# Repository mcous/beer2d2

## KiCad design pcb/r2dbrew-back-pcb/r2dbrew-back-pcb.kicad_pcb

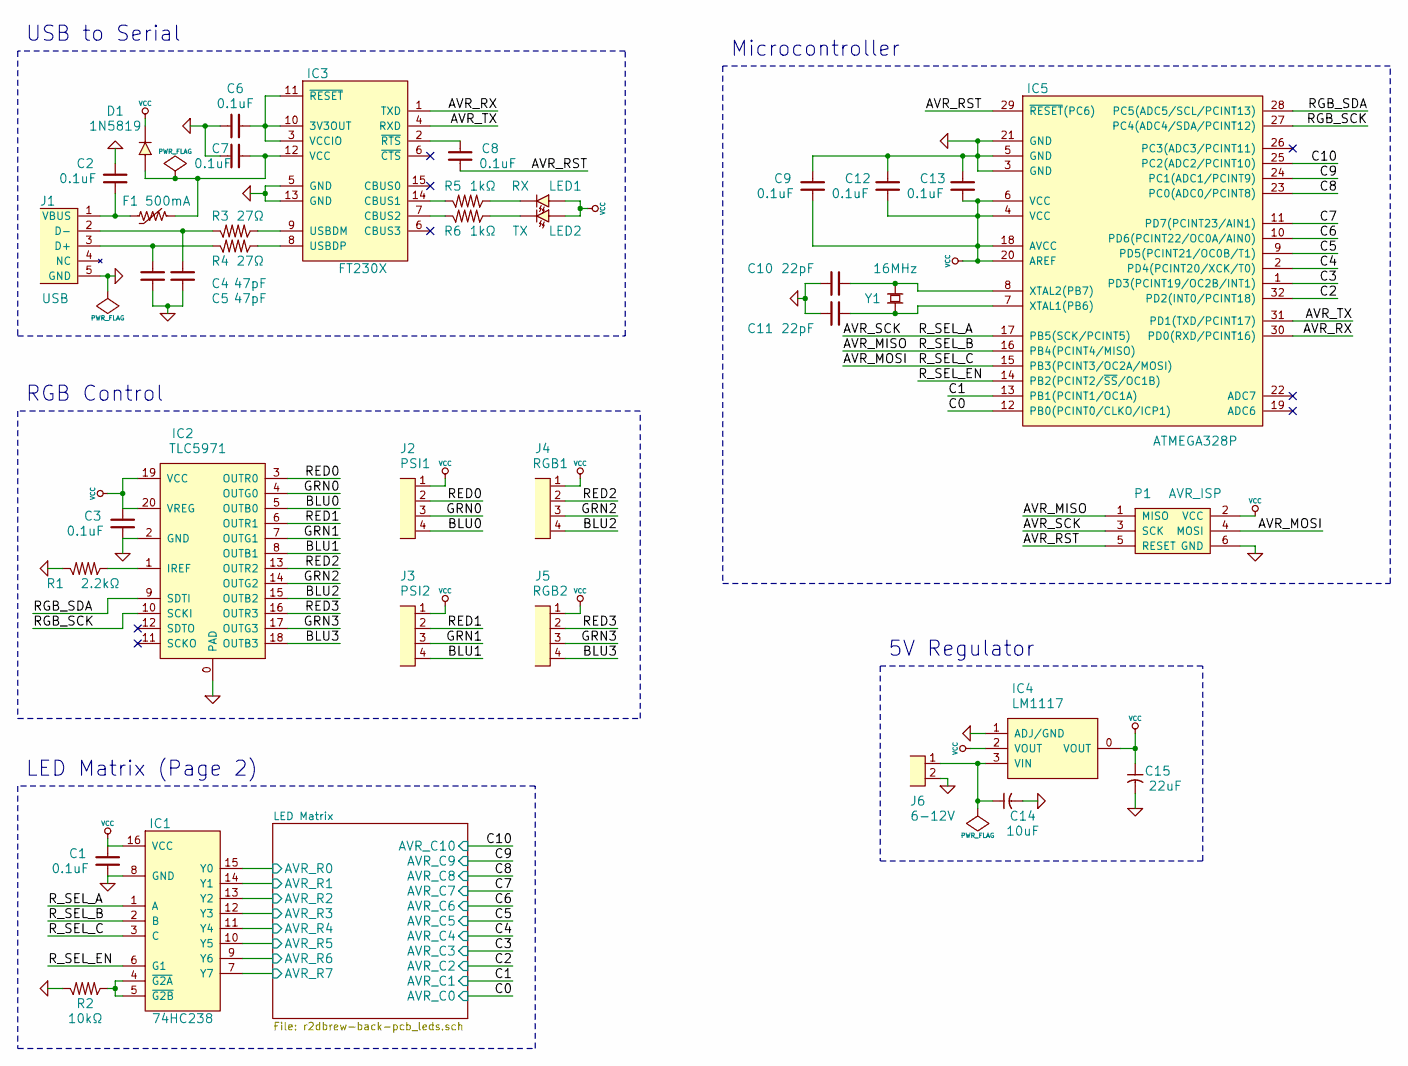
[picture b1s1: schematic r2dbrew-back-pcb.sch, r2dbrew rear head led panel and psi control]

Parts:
C1, C2, C3, C6, C7, C8, C9, C12, C13: 0.1uF
C4, C5: 47pF
C10, C11: 22pF
C14: 10uF
C15: 22uF
D1: 1N5819
F1: 500mA
IC1: 74HC238
IC2: TLC5971; Part TLC5971PWP
IC3: FT230X
IC4: LM1117
IC5: ATMEGA328P
J1: USB
J2: PSI1
J3: PSI2
J4: RGB1
J5: RGB2
J6: 6-12V
LED1: RX
LED2: TX
P1: AVR_ISP
R1: 2.2kΩ
R2: 10kΩ
R3, R4: 27Ω
R5, R6: 1kΩ
Y1: 16MHz

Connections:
/AVR_MISO: IC1.2 (B), IC5.16 (PB4(PCINT4/MISO)), P1.1 (MISO)
/AVR_MOSI: IC1.3 (C), IC5.15 (PB3(PCINT3/OC2A/MOSI)), P1.4 (MOSI)
/AVR_RST: C8.1, IC5.29 (~RESET~(PC6)), P1.5 (RESET)
/AVR_RX: IC3.1 (TXD), IC5.30 (PD0(RXD/PCINT16))
/AVR_SCK: IC1.1 (A), IC5.17 (PB5(SCK/PCINT5)), P1.3 (SCK)
/AVR_TX: IC3.4 (RXD), IC5.31 (PD1(TXD/PCINT17))
/BLU0: IC2.5 (OUTB0), J2.4
/BLU1: IC2.8 (OUTB1), J3.4
/BLU2: IC2.15 (OUTB2), J4.4
/BLU3: IC2.18 (OUTB3), J5.4
/GRN0: IC2.4 (OUTG0), J2.3
/GRN1: IC2.7 (OUTG1), J3.3
/GRN2: IC2.14 (OUTG2), J4.3
/GRN3: IC2.17 (OUTG3), J5.3
/LED Matrix/AVR_C0: IC5.12 (PB0(PCINT0/CLKO/ICP1)); also elsewhere on the board
/LED Matrix/AVR_C1: IC5.13 (PB1(PCINT1/OC1A)); also elsewhere on the board
/LED Matrix/AVR_C2: IC5.32 (PD2(INT0/PCINT18)); also elsewhere on the board
/LED Matrix/AVR_C3: IC5.1 (PD3(PCINT19/OC2B/INT1)); also elsewhere on the board
/LED Matrix/AVR_C4: IC5.2 (PD4(PCINT20/XCK/T0)); also elsewhere on the board
/LED Matrix/AVR_C5: IC5.9 (PD5(PCINT21/OC0B/T1)); also elsewhere on the board
/LED Matrix/AVR_C6: IC5.10 (PD6(PCINT22/OC0A/AIN0)); also elsewhere on the board
/LED Matrix/AVR_C7: IC5.11 (PD7(PCINT23/AIN1)); also elsewhere on the board
/LED Matrix/AVR_C8: IC5.23 (PC0(ADC0/PCINT8)); also elsewhere on the board
/LED Matrix/AVR_C9: IC5.24 (PC1(ADC1/PCINT9)); also elsewhere on the board
/LED Matrix/AVR_C10: IC5.25 (PC2(ADC2/PCINT10)); also elsewhere on the board
/LED Matrix/AVR_R0: IC1.15 (Y0); also elsewhere on the board
/LED Matrix/AVR_R1: IC1.14 (Y1); also elsewhere on the board
/LED Matrix/AVR_R2: IC1.13 (Y2); also elsewhere on the board
/LED Matrix/AVR_R3: IC1.12 (Y3); also elsewhere on the board
/LED Matrix/AVR_R4: IC1.11 (Y4); also elsewhere on the board
/LED Matrix/AVR_R5: IC1.10 (Y5); also elsewhere on the board
/LED Matrix/AVR_R6: IC1.9 (Y6); also elsewhere on the board
/LED Matrix/AVR_R7: IC1.7 (Y7); also elsewhere on the board
/RED0: IC2.3 (OUTR0), J2.2
/RED1: IC2.6 (OUTR1), J3.2
/RED2: IC2.13 (OUTR2), J4.2
/RED3: IC2.16 (OUTR3), J5.2
/RGB_SCK: IC2.10 (SCKI), IC5.27 (PC4(ADC4/SDA/PCINT12))
/RGB_SDA: IC2.9 (SDTI), IC5.28 (PC5(ADC5/SCL/PCINT13))
/R_SEL_EN: IC1.6 (G1), IC5.14 (PB2(PCINT2/~SS~/OC1B))
GND: C1.1, C2.2, C3.1, C4.1, C5.1, C6.1, C7.1, C9.1, C10.1, C11.1, C12.1, C13.1, C14.2, C15.2, IC1.8 (GND), IC2.0 (PAD), IC2.2 (GND), IC3.5 (GND), IC3.13 (GND), IC4.1 (ADJ/GND), IC5.3 (GND), IC5.5 (GND), IC5.21 (GND), J1.5 (GND), J6.2, P1.6 (GND), R1.1, R2.1; also elsewhere on the board
unnamed: C2.1, F1.1, J1.1 (VBUS)
unnamed: C4.2, J1.3 (D+), R4.1
unnamed: C5.2, J1.2 (D-), R3.1
unnamed: C6.2, IC3.3 (VCCIO), IC3.10 (3V3OUT), IC3.11 (~RESET~)
unnamed: C7.2, D1.2 (A), F1.2, IC3.12 (VCC)
unnamed: C8.2, IC3.2 (~RTS~)
unnamed: C10.2, IC5.8 (XTAL2(PB7)), Y1.2
unnamed: C11.2, IC5.7 (XTAL1(PB6)), Y1.1
unnamed: C14.1, IC4.3 (VIN), J6.1
unnamed: IC1.4 (~G2A~), IC1.5 (~G2B~), R2.2
unnamed: IC2.1 (IREF), R1.2
unnamed: IC3.7 (CBUS2), R6.1
unnamed: IC3.8 (USBDP), R4.2
unnamed: IC3.9 (USBDM), R3.2
unnamed: IC3.14 (CBUS1), R5.1
unnamed: LED1.1 (C), R5.2
unnamed: LED2.1 (C), R6.2
VCC: C1.2, C3.2, C9.2, C12.2, C13.2, C15.1, D1.1 (C), IC1.16 (VCC), IC2.19 (VCC), IC2.20 (VREG), IC4.0 (VOUT), IC4.2 (VOUT), IC5.4 (VCC), IC5.6 (VCC), IC5.18 (AVCC), IC5.20 (AREF), J2.1, J3.1, J4.1, J5.1, LED1.2 (A), LED2.2 (A), P1.2 (VCC); also elsewhere on the board

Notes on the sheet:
LED Matrix (Page 2)
RGB Control
USB to Serial
Microcontroller
5V Regulator

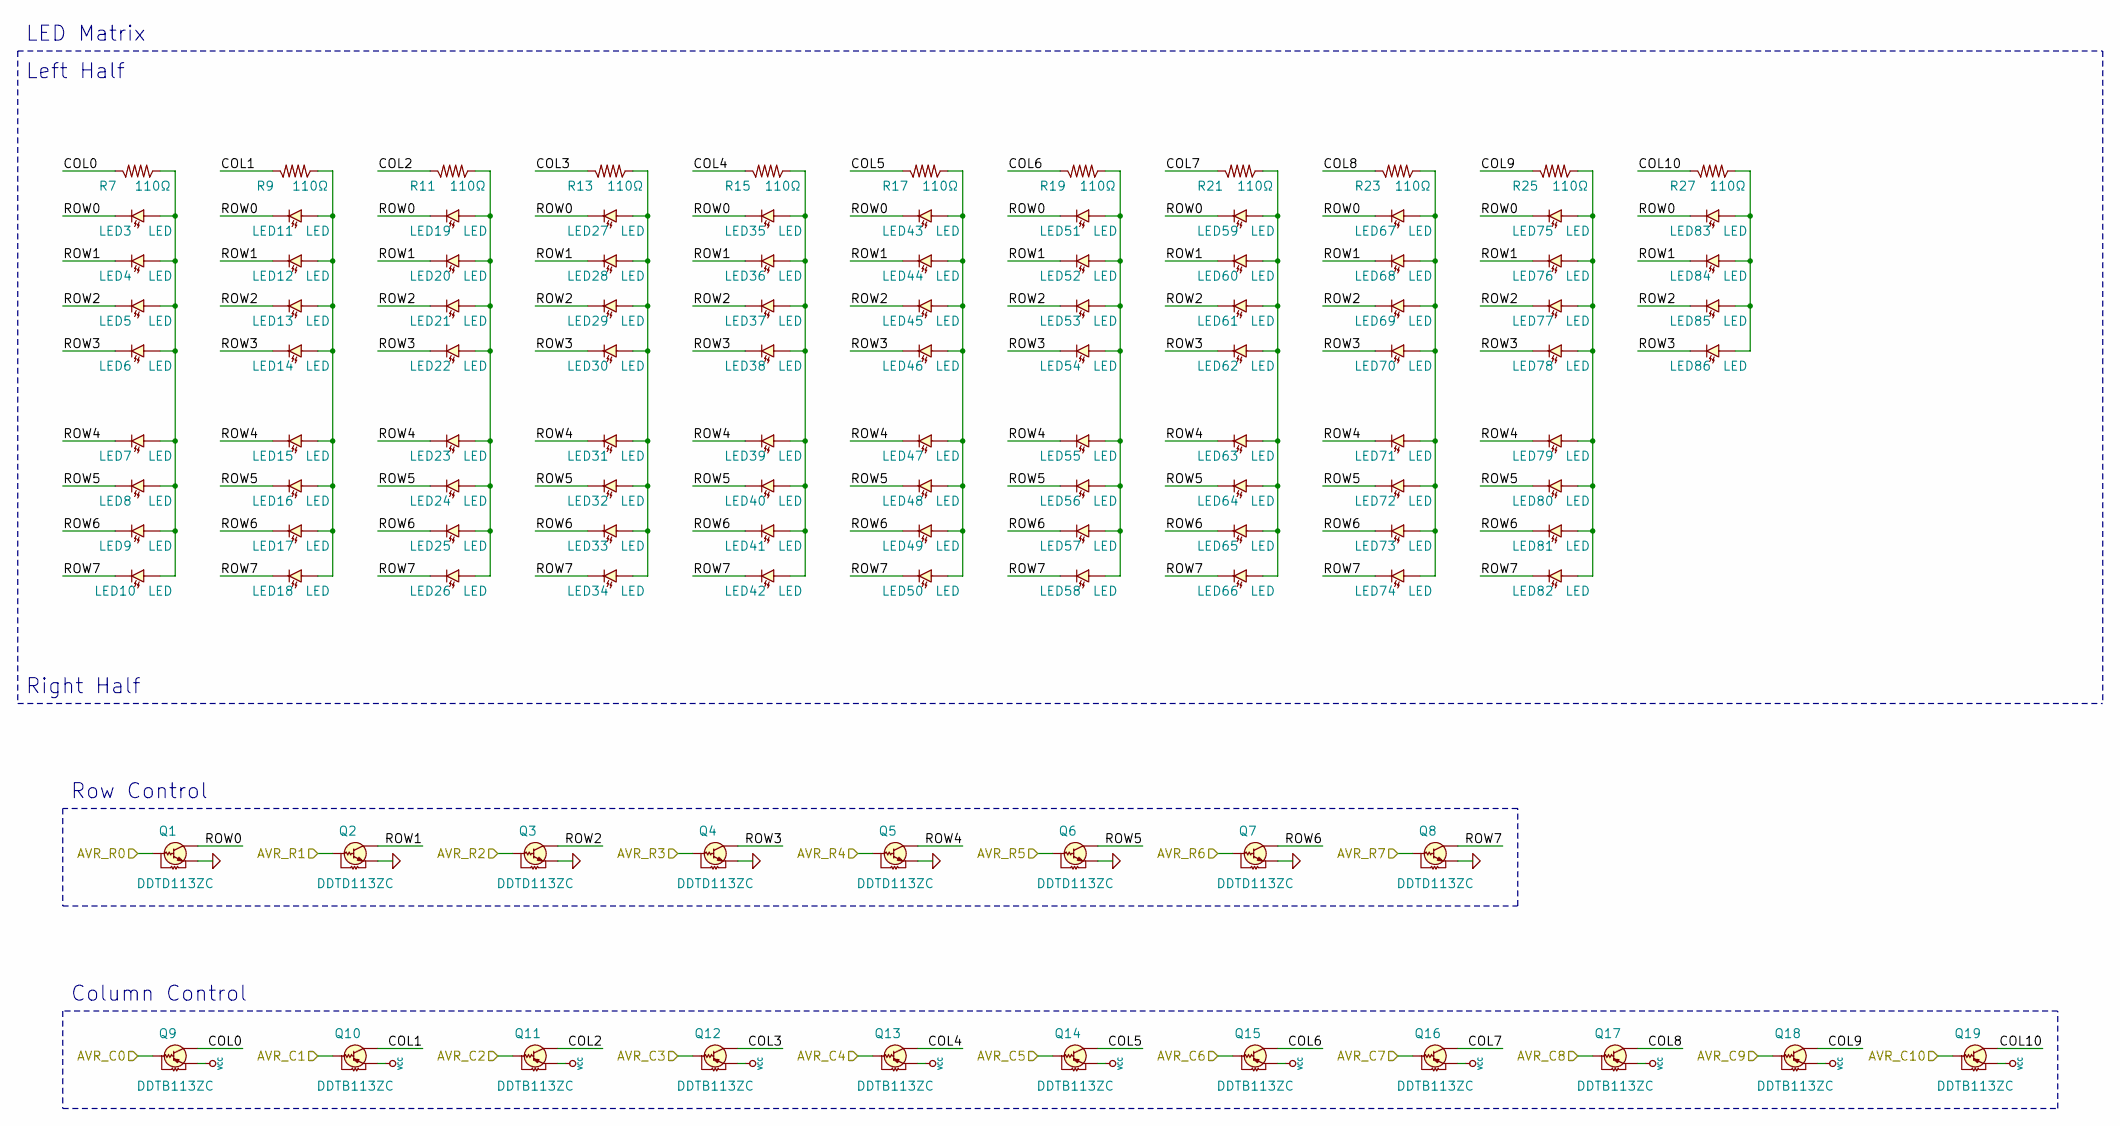
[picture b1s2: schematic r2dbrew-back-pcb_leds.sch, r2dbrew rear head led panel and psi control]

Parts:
LED3, LED4, LED5, LED6, LED7, LED8, LED9, LED10, LED11, LED12, LED13, LED14, LED15, LED16, LED17, LED18, LED19, LED20, LED21, LED22, LED23, LED24, LED25, LED26, LED27, LED28, LED29, LED30, LED31, LED32, LED33, LED34, LED35, LED36, LED37, LED38, LED39, LED40, LED41, LED42, LED43, LED44, LED45, LED46, LED47, LED48, LED49, LED50, LED51, LED52, LED53, LED54, LED55, LED56, LED57, LED58, LED59, LED60, LED61, LED62, LED63, LED64, LED65, LED66, LED67, LED68, LED69, LED70, LED71, LED72, LED73, LED74, LED75, LED76, LED77, LED78, LED79, LED80, LED81, LED82, LED83, LED84, LED85, LED86: LED
Q1, Q2, Q3, Q4, Q5, Q6, Q7, Q8: DDTD113ZC
Q9, Q10, Q11, Q12, Q13, Q14, Q15, Q16, Q17, Q18, Q19: DDTB113ZC
R7, R9, R11, R13, R15, R17, R19, R21, R23, R25, R27: 110Ω

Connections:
/LED Matrix/AVR_C0: Q9.1 (B); also elsewhere on the board
/LED Matrix/AVR_C1: Q10.1 (B); also elsewhere on the board
/LED Matrix/AVR_C2: Q11.1 (B); also elsewhere on the board
/LED Matrix/AVR_C3: Q12.1 (B); also elsewhere on the board
/LED Matrix/AVR_C4: Q13.1 (B); also elsewhere on the board
/LED Matrix/AVR_C5: Q14.1 (B); also elsewhere on the board
/LED Matrix/AVR_C6: Q15.1 (B); also elsewhere on the board
/LED Matrix/AVR_C7: Q16.1 (B); also elsewhere on the board
/LED Matrix/AVR_C8: Q17.1 (B); also elsewhere on the board
/LED Matrix/AVR_C9: Q18.1 (B); also elsewhere on the board
/LED Matrix/AVR_C10: Q19.1 (B); also elsewhere on the board
/LED Matrix/AVR_R0: Q1.1 (B); also elsewhere on the board
/LED Matrix/AVR_R1: Q2.1 (B); also elsewhere on the board
/LED Matrix/AVR_R2: Q3.1 (B); also elsewhere on the board
/LED Matrix/AVR_R3: Q4.1 (B); also elsewhere on the board
/LED Matrix/AVR_R4: Q5.1 (B); also elsewhere on the board
/LED Matrix/AVR_R5: Q6.1 (B); also elsewhere on the board
/LED Matrix/AVR_R6: Q7.1 (B); also elsewhere on the board
/LED Matrix/AVR_R7: Q8.1 (B); also elsewhere on the board
/LED Matrix/COL0: Q9.3 (C), R7.1
/LED Matrix/COL1: Q10.3 (C), R9.1
/LED Matrix/COL2: Q11.3 (C), R11.1
/LED Matrix/COL3: Q12.3 (C), R13.1
/LED Matrix/COL4: Q13.3 (C), R15.1
/LED Matrix/COL5: Q14.3 (C), R17.1
/LED Matrix/COL6: Q15.3 (C), R19.1
/LED Matrix/COL7: Q16.3 (C), R21.1
/LED Matrix/COL8: Q17.3 (C), R23.1
/LED Matrix/COL9: Q18.3 (C), R25.1
/LED Matrix/COL10: Q19.3 (C), R27.1
/LED Matrix/ROW0: LED3.1 (C), LED11.1 (C), LED19.1 (C), LED27.1 (C), LED35.1 (C), LED43.1 (C), LED51.1 (C), LED59.1 (C), LED67.1 (C), LED75.1 (C), LED83.1 (C), Q1.3 (C)
/LED Matrix/ROW1: LED4.1 (C), LED12.1 (C), LED20.1 (C), LED28.1 (C), LED36.1 (C), LED44.1 (C), LED52.1 (C), LED60.1 (C), LED68.1 (C), LED76.1 (C), LED84.1 (C), Q2.3 (C)
/LED Matrix/ROW2: LED5.1 (C), LED13.1 (C), LED21.1 (C), LED29.1 (C), LED37.1 (C), LED45.1 (C), LED53.1 (C), LED61.1 (C), LED69.1 (C), LED77.1 (C), LED85.1 (C), Q3.3 (C)
/LED Matrix/ROW3: LED6.1 (C), LED14.1 (C), LED22.1 (C), LED30.1 (C), LED38.1 (C), LED46.1 (C), LED54.1 (C), LED62.1 (C), LED70.1 (C), LED78.1 (C), LED86.1 (C), Q4.3 (C)
/LED Matrix/ROW4: LED7.1 (C), LED15.1 (C), LED23.1 (C), LED31.1 (C), LED39.1 (C), LED47.1 (C), LED55.1 (C), LED63.1 (C), LED71.1 (C), LED79.1 (C), Q5.3 (C)
/LED Matrix/ROW5: LED8.1 (C), LED16.1 (C), LED24.1 (C), LED32.1 (C), LED40.1 (C), LED48.1 (C), LED56.1 (C), LED64.1 (C), LED72.1 (C), LED80.1 (C), Q6.3 (C)
/LED Matrix/ROW6: LED9.1 (C), LED17.1 (C), LED25.1 (C), LED33.1 (C), LED41.1 (C), LED49.1 (C), LED57.1 (C), LED65.1 (C), LED73.1 (C), LED81.1 (C), Q7.3 (C)
/LED Matrix/ROW7: LED10.1 (C), LED18.1 (C), LED26.1 (C), LED34.1 (C), LED42.1 (C), LED50.1 (C), LED58.1 (C), LED66.1 (C), LED74.1 (C), LED82.1 (C), Q8.3 (C)
GND: Q1.2 (E), Q2.2 (E), Q3.2 (E), Q4.2 (E), Q5.2 (E), Q6.2 (E), Q7.2 (E), Q8.2 (E); also elsewhere on the board
unnamed: LED3.2 (A), LED4.2 (A), LED5.2 (A), LED6.2 (A), LED7.2 (A), LED8.2 (A), LED9.2 (A), LED10.2 (A), R7.2
unnamed: LED11.2 (A), LED12.2 (A), LED13.2 (A), LED14.2 (A), LED15.2 (A), LED16.2 (A), LED17.2 (A), LED18.2 (A), R9.2
unnamed: LED19.2 (A), LED20.2 (A), LED21.2 (A), LED22.2 (A), LED23.2 (A), LED24.2 (A), LED25.2 (A), LED26.2 (A), R11.2
unnamed: LED27.2 (A), LED28.2 (A), LED29.2 (A), LED30.2 (A), LED31.2 (A), LED32.2 (A), LED33.2 (A), LED34.2 (A), R13.2
unnamed: LED35.2 (A), LED36.2 (A), LED37.2 (A), LED38.2 (A), LED39.2 (A), LED40.2 (A), LED41.2 (A), LED42.2 (A), R15.2
unnamed: LED43.2 (A), LED44.2 (A), LED45.2 (A), LED46.2 (A), LED47.2 (A), LED48.2 (A), LED49.2 (A), LED50.2 (A), R17.2
unnamed: LED51.2 (A), LED52.2 (A), LED53.2 (A), LED54.2 (A), LED55.2 (A), LED56.2 (A), LED57.2 (A), LED58.2 (A), R19.2
unnamed: LED59.2 (A), LED60.2 (A), LED61.2 (A), LED62.2 (A), LED63.2 (A), LED64.2 (A), LED65.2 (A), LED66.2 (A), R21.2
unnamed: LED67.2 (A), LED68.2 (A), LED69.2 (A), LED70.2 (A), LED71.2 (A), LED72.2 (A), LED73.2 (A), LED74.2 (A), R23.2
unnamed: LED75.2 (A), LED76.2 (A), LED77.2 (A), LED78.2 (A), LED79.2 (A), LED80.2 (A), LED81.2 (A), LED82.2 (A), R25.2
unnamed: LED83.2 (A), LED84.2 (A), LED85.2 (A), LED86.2 (A), R27.2
VCC: Q9.2 (E), Q10.2 (E), Q11.2 (E), Q12.2 (E), Q13.2 (E), Q14.2 (E), Q15.2 (E), Q16.2 (E), Q17.2 (E), Q18.2 (E), Q19.2 (E); also elsewhere on the board

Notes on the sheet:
LED Matrix
Right Half
Row Control
Column Control
Left Half

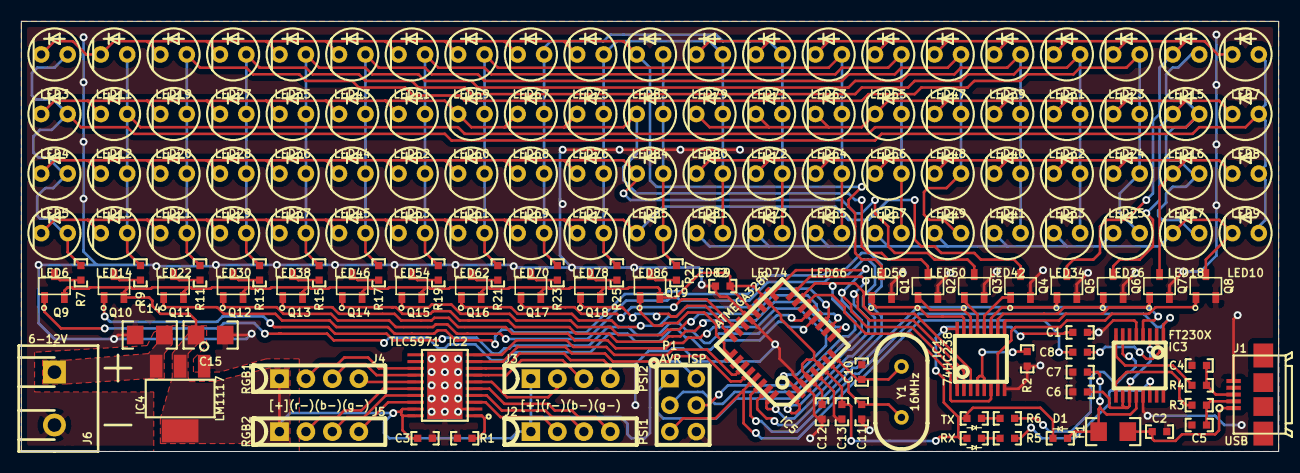
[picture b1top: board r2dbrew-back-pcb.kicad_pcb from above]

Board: 2 copper layers, 120.6 x 41.3 mm, 152 parts (0 on the bottom side), 89 nets.

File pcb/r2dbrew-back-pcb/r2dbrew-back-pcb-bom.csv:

Reference, Value, Footprint, Datasheet, Manufacturer, Part
J6,6-12V,,
IC4,LM1117,,
C14,10uF,,
C15,22uF,,
IC5,ATMEGA328P,,
IC1,74HC238,,
C1,0.1uF,,
R2,10kΩ,,
Y1,16MHz,,
C11,22pF,,
C10,22pF,,
C13,0.1uF,,
C12,0.1uF,,
C9,0.1uF,,
P1,AVR_ISP,,
J1,USB,,
R3,27Ω,,
R4,27Ω,,
C4,47pF,,
C5,47pF,,
IC3,FT230X,,
C6,0.1uF,,
C7,0.1uF,,
C2,0.1uF,,
F1,500mA,,
D1,1N5819,,
C8,0.1uF,,
R5,1kΩ,,
R6,1kΩ,,
LED1,RX,,
LED2,TX,,
IC2,TLC5971,,,TI,TLC5971PWP
C3,0.1uF,,
R1,2.2kΩ,,
J2,PSI1,,
J3,PSI2,,
J4,RGB1,,
J5,RGB2,,
LED4,LED,,
LED5,LED,,
LED6,LED,,
Q1,DDTD113ZC,,
Q2,DDTD113ZC,,
Q3,DDTD113ZC,,
Q4,DDTD113ZC,,
Q5,DDTD113ZC,,
Q6,DDTD113ZC,,
Q7,DDTD113ZC,,
Q8,DDTD113ZC,,
Q9,DDTB113ZC,,
Q10,DDTB113ZC,,
Q11,DDTB113ZC,,
Q12,DDTB113ZC,,
Q13,DDTB113ZC,,
Q14,DDTB113ZC,,
Q15,DDTB113ZC,,
Q16,DDTB113ZC,,
Q17,DDTB113ZC,,
Q18,DDTB113ZC,,
Q19,DDTB113ZC,,
R7,110Ω,,
LED3,LED,,
LED12,LED,,
LED13,LED,,
LED14,LED,,
R9,110Ω,,
LED11,LED,,
LED20,LED,,
LED21,LED,,
LED22,LED,,
R11,110Ω,,
LED19,LED,,
LED28,LED,,
LED29,LED,,
LED30,LED,,
R13,110Ω,,
LED27,LED,,
LED36,LED,,
LED37,LED,,
LED38,LED,,
R15,110Ω,,
LED35,LED,,
LED44,LED,,
LED45,LED,,
LED46,LED,,
R17,110Ω,,
LED43,LED,,
LED52,LED,,
LED53,LED,,
LED54,LED,,
R19,110Ω,,
LED51,LED,,
LED60,LED,,
LED61,LED,,
LED62,LED,,
R21,110Ω,,
LED59,LED,,
LED68,LED,,
LED69,LED,,
LED70,LED,,
R23,110Ω,,
LED67,LED,,
LED76,LED,,
LED77,LED,,
LED78,LED,,
R25,110Ω,,
LED75,LED,,
LED84,LED,,
LED85,LED,,
LED86,LED,,
R27,110Ω,,
LED83,LED,,
LED8,LED,,
LED9,LED,,
LED10,LED,,
LED7,LED,,
LED16,LED,,
LED17,LED,,
LED18,LED,,
LED15,LED,,
LED24,LED,,
LED25,LED,,
LED26,LED,,
LED23,LED,,
LED32,LED,,
LED33,LED,,
LED34,LED,,
LED31,LED,,
LED40,LED,,
LED41,LED,,
LED42,LED,,
LED39,LED,,
LED48,LED,,
LED49,LED,,
LED50,LED,,
LED47,LED,,
LED56,LED,,
LED57,LED,,
LED58,LED,,
LED55,LED,,
LED64,LED,,
LED65,LED,,
LED66,LED,,
LED63,LED,,
LED72,LED,,
LED73,LED,,
LED74,LED,,
LED71,LED,,
LED80,LED,,
LED81,LED,,
LED82,LED,,
LED79,LED,,

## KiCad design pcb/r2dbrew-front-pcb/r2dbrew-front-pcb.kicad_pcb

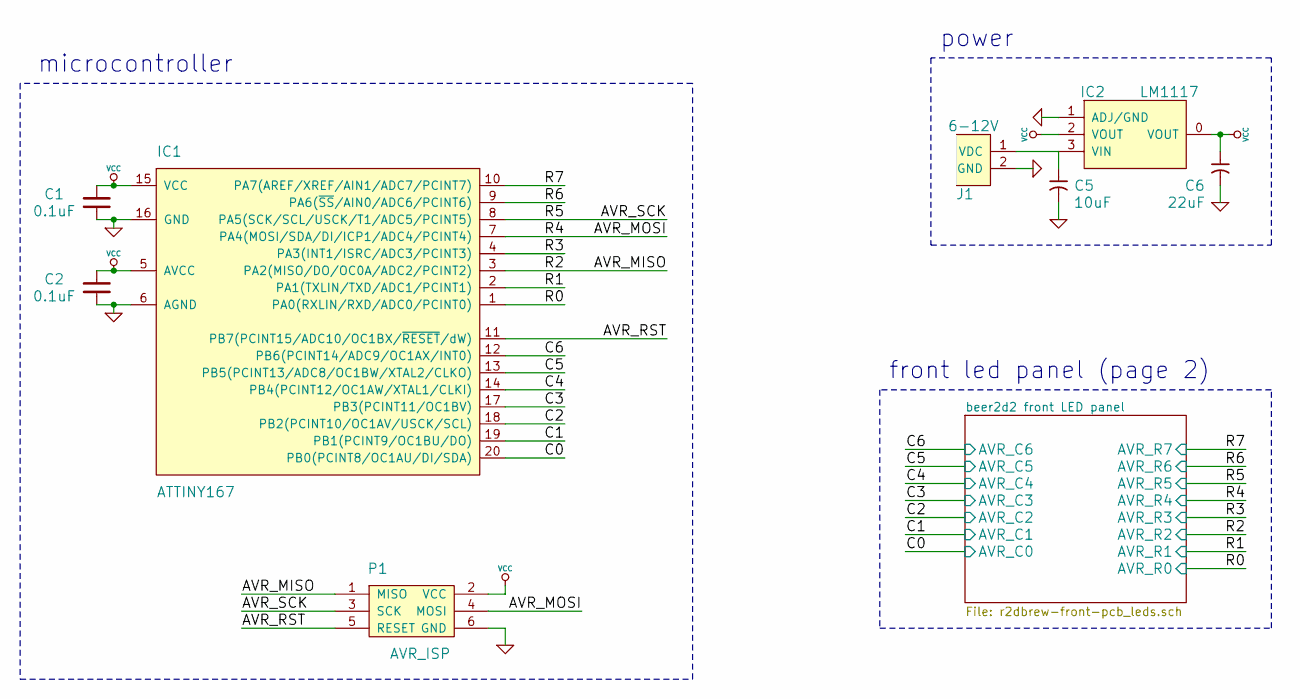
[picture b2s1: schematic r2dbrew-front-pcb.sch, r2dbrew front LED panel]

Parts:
C1, C2: 0.1uF
C5: 10uF
C6: 22uF
IC1: ATTINY167
IC2: LM1117
J1: 6-12V
P1: AVR_ISP

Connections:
/AVR_RST: IC1.11 (PB7(PCINT15/ADC10/OC1BX/~RESET~/dW)), P1.5 (RESET)
/beer2d2 front LED panel/AVR_C0: IC1.20 (PB0(PCINT8/OC1AU/DI/SDA)); also elsewhere on the board
/beer2d2 front LED panel/AVR_C1: IC1.19 (PB1(PCINT9/OC1BU/DO)); also elsewhere on the board
/beer2d2 front LED panel/AVR_C2: IC1.18 (PB2(PCINT10/OC1AV/USCK/SCL)); also elsewhere on the board
/beer2d2 front LED panel/AVR_C3: IC1.17 (PB3(PCINT11/OC1BV)); also elsewhere on the board
/beer2d2 front LED panel/AVR_C4: IC1.14 (PB4(PCINT12/OC1AW/XTAL1/CLKI)); also elsewhere on the board
/beer2d2 front LED panel/AVR_C5: IC1.13 (PB5(PCINT13/ADC8/OC1BW/XTAL2/CLKO)); also elsewhere on the board
/beer2d2 front LED panel/AVR_C6: IC1.12 (PB6(PCINT14/ADC9/OC1AX/INT0)); also elsewhere on the board
/beer2d2 front LED panel/AVR_R0: IC1.1 (PA0(RXLIN/RXD/ADC0/PCINT0)); also elsewhere on the board
/beer2d2 front LED panel/AVR_R1: IC1.2 (PA1(TXLIN/TXD/ADC1/PCINT1)); also elsewhere on the board
/beer2d2 front LED panel/AVR_R2: IC1.3 (PA2(MISO/DO/OC0A/ADC2/PCINT2)), P1.1 (MISO); also elsewhere on the board
/beer2d2 front LED panel/AVR_R3: IC1.4 (PA3(INT1/ISRC/ADC3/PCINT3)); also elsewhere on the board
/beer2d2 front LED panel/AVR_R4: IC1.7 (PA4(MOSI/SDA/DI/ICP1/ADC4/PCINT4)), P1.4 (MOSI); also elsewhere on the board
/beer2d2 front LED panel/AVR_R5: IC1.8 (PA5(SCK/SCL/USCK/T1/ADC5/PCINT5)), P1.3 (SCK); also elsewhere on the board
/beer2d2 front LED panel/AVR_R6: IC1.9 (PA6(~SS~/AIN0/ADC6/PCINT6)); also elsewhere on the board
/beer2d2 front LED panel/AVR_R7: IC1.10 (PA7(AREF/XREF/AIN1/ADC7/PCINT7)); also elsewhere on the board
GND: C1.1, C2.1, C5.2, C6.2, IC1.6 (AGND), IC1.16 (GND), IC2.1 (ADJ/GND), J1.2 (GND), P1.6 (GND); also elsewhere on the board
unnamed: C5.1, IC2.3 (VIN), J1.1 (VDC)
VCC: C1.2, C2.2, C6.1, IC1.5 (AVCC), IC1.15 (VCC), IC2.0 (VOUT), IC2.2 (VOUT), P1.2 (VCC); also elsewhere on the board

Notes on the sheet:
power
microcontroller
front led panel (page 2)

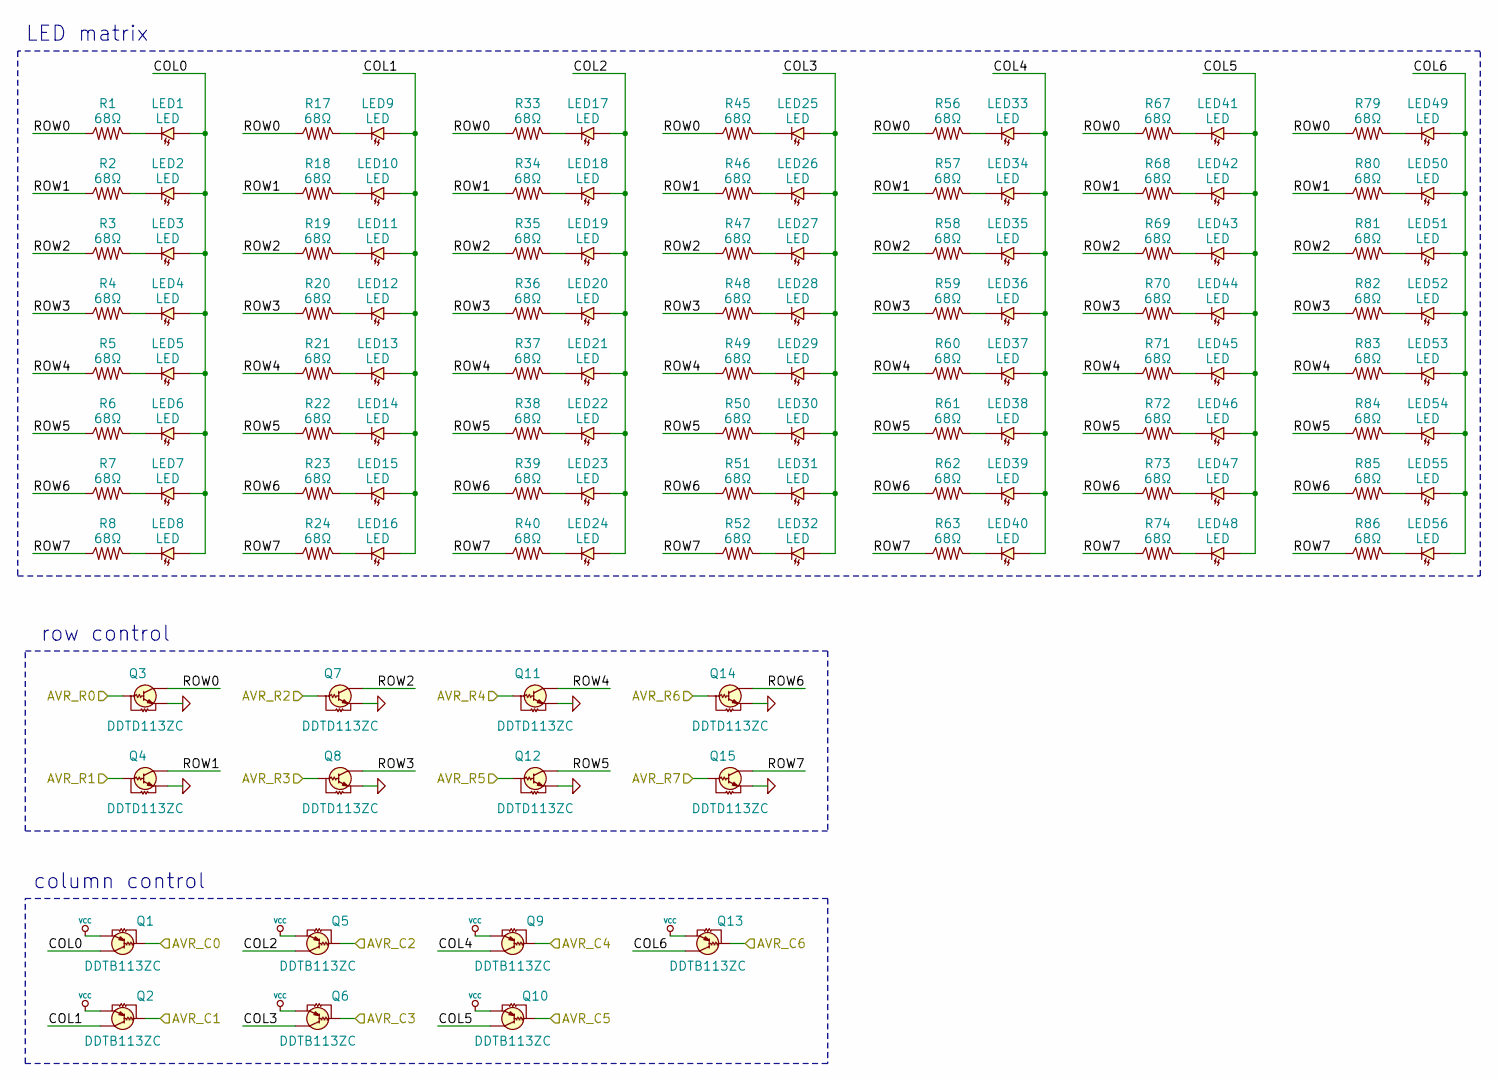
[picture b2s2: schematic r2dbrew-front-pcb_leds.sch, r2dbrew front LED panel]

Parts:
LED1, LED2, LED3, LED4, LED5, LED6, LED7, LED8, LED9, LED10, LED11, LED12, LED13, LED14, LED15, LED16, LED17, LED18, LED19, LED20, LED21, LED22, LED23, LED24, LED25, LED26, LED27, LED28, LED29, LED30, LED31, LED32, LED33, LED34, LED35, LED36, LED37, LED38, LED39, LED40, LED41, LED42, LED43, LED44, LED45, LED46, LED47, LED48, LED49, LED50, LED51, LED52, LED53, LED54, LED55, LED56: LED
Q1, Q2, Q5, Q6, Q9, Q10, Q13: DDTB113ZC; Part DDTB113ZC-7-F
Q3, Q4, Q7, Q8, Q11, Q12, Q14, Q15: DDTD113ZC; Part DDTD113ZC-7-F
R1, R2, R3, R4, R5, R6, R7, R8, R17, R18, R19, R20, R21, R22, R23, R24, R33, R34, R35, R36, R37, R38, R39, R40, R45, R46, R47, R48, R49, R50, R51, R52, R56, R57, R58, R59, R60, R61, R62, R63, R67, R68, R69, R70, R71, R72, R73, R74, R79, R80, R81, R82, R83, R84, R85, R86: 68Ω; Part RC1608J680CS

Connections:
/beer2d2 front LED panel/AVR_C0: Q1.1 (B); also elsewhere on the board
/beer2d2 front LED panel/AVR_C1: Q2.1 (B); also elsewhere on the board
/beer2d2 front LED panel/AVR_C2: Q5.1 (B); also elsewhere on the board
/beer2d2 front LED panel/AVR_C3: Q6.1 (B); also elsewhere on the board
/beer2d2 front LED panel/AVR_C4: Q9.1 (B); also elsewhere on the board
/beer2d2 front LED panel/AVR_C5: Q10.1 (B); also elsewhere on the board
/beer2d2 front LED panel/AVR_C6: Q13.1 (B); also elsewhere on the board
/beer2d2 front LED panel/AVR_R0: Q3.1 (B); also elsewhere on the board
/beer2d2 front LED panel/AVR_R1: Q4.1 (B); also elsewhere on the board
/beer2d2 front LED panel/AVR_R2: Q7.1 (B); also elsewhere on the board
/beer2d2 front LED panel/AVR_R3: Q8.1 (B); also elsewhere on the board
/beer2d2 front LED panel/AVR_R4: Q11.1 (B); also elsewhere on the board
/beer2d2 front LED panel/AVR_R5: Q12.1 (B); also elsewhere on the board
/beer2d2 front LED panel/AVR_R6: Q14.1 (B); also elsewhere on the board
/beer2d2 front LED panel/AVR_R7: Q15.1 (B); also elsewhere on the board
/beer2d2 front LED panel/COL0: LED1.2 (A), LED2.2 (A), LED3.2 (A), LED4.2 (A), LED5.2 (A), LED6.2 (A), LED7.2 (A), LED8.2 (A), Q1.3 (C)
/beer2d2 front LED panel/COL1: LED9.2 (A), LED10.2 (A), LED11.2 (A), LED12.2 (A), LED13.2 (A), LED14.2 (A), LED15.2 (A), LED16.2 (A), Q2.3 (C)
/beer2d2 front LED panel/COL2: LED17.2 (A), LED18.2 (A), LED19.2 (A), LED20.2 (A), LED21.2 (A), LED22.2 (A), LED23.2 (A), LED24.2 (A), Q5.3 (C)
/beer2d2 front LED panel/COL3: LED25.2 (A), LED26.2 (A), LED27.2 (A), LED28.2 (A), LED29.2 (A), LED30.2 (A), LED31.2 (A), LED32.2 (A), Q6.3 (C)
/beer2d2 front LED panel/COL4: LED33.2 (A), LED34.2 (A), LED35.2 (A), LED36.2 (A), LED37.2 (A), LED38.2 (A), LED39.2 (A), LED40.2 (A), Q9.3 (C)
/beer2d2 front LED panel/COL5: LED41.2 (A), LED42.2 (A), LED43.2 (A), LED44.2 (A), LED45.2 (A), LED46.2 (A), LED47.2 (A), LED48.2 (A), Q10.3 (C)
/beer2d2 front LED panel/COL6: LED49.2 (A), LED50.2 (A), LED51.2 (A), LED52.2 (A), LED53.2 (A), LED54.2 (A), LED55.2 (A), LED56.2 (A), Q13.3 (C)
/beer2d2 front LED panel/ROW0: Q3.3 (C), R1.2, R17.2, R33.2, R45.2, R56.2, R67.2, R79.2
/beer2d2 front LED panel/ROW1: Q4.3 (C), R2.2, R18.2, R34.2, R46.2, R57.2, R68.2, R80.2
/beer2d2 front LED panel/ROW2: Q7.3 (C), R3.2, R19.2, R35.2, R47.2, R58.2, R69.2, R81.2
/beer2d2 front LED panel/ROW3: Q8.3 (C), R4.2, R20.2, R36.2, R48.2, R59.2, R70.2, R82.2
/beer2d2 front LED panel/ROW4: Q11.3 (C), R5.2, R21.2, R37.2, R49.2, R60.2, R71.2, R83.2
/beer2d2 front LED panel/ROW5: Q12.3 (C), R6.2, R22.2, R38.2, R50.2, R61.2, R72.2, R84.2
/beer2d2 front LED panel/ROW6: Q14.3 (C), R7.2, R23.2, R39.2, R51.2, R62.2, R73.2, R85.2
/beer2d2 front LED panel/ROW7: Q15.3 (C), R8.2, R24.2, R40.2, R52.2, R63.2, R74.2, R86.2
GND: Q3.2 (E), Q4.2 (E), Q7.2 (E), Q8.2 (E), Q11.2 (E), Q12.2 (E), Q14.2 (E), Q15.2 (E); also elsewhere on the board
unnamed: LED1.1 (C), R1.1
unnamed: LED2.1 (C), R2.1
unnamed: LED3.1 (C), R3.1
unnamed: LED4.1 (C), R4.1
unnamed: LED5.1 (C), R5.1
unnamed: LED6.1 (C), R6.1
unnamed: LED7.1 (C), R7.1
unnamed: LED8.1 (C), R8.1
unnamed: LED9.1 (C), R17.1
unnamed: LED10.1 (C), R18.1
unnamed: LED11.1 (C), R19.1
unnamed: LED12.1 (C), R20.1
unnamed: LED13.1 (C), R21.1
unnamed: LED14.1 (C), R22.1
unnamed: LED15.1 (C), R23.1
unnamed: LED16.1 (C), R24.1
unnamed: LED17.1 (C), R33.1
unnamed: LED18.1 (C), R34.1
unnamed: LED19.1 (C), R35.1
unnamed: LED20.1 (C), R36.1
unnamed: LED21.1 (C), R37.1
unnamed: LED22.1 (C), R38.1
unnamed: LED23.1 (C), R39.1
unnamed: LED24.1 (C), R40.1
unnamed: LED25.1 (C), R45.1
unnamed: LED26.1 (C), R46.1
unnamed: LED27.1 (C), R47.1
unnamed: LED28.1 (C), R48.1
unnamed: LED29.1 (C), R49.1
unnamed: LED30.1 (C), R50.1
unnamed: LED31.1 (C), R51.1
unnamed: LED32.1 (C), R52.1
unnamed: LED33.1 (C), R56.1
unnamed: LED34.1 (C), R57.1
unnamed: LED35.1 (C), R58.1
unnamed: LED36.1 (C), R59.1
unnamed: LED37.1 (C), R60.1
unnamed: LED38.1 (C), R61.1
unnamed: LED39.1 (C), R62.1
unnamed: LED40.1 (C), R63.1
unnamed: LED41.1 (C), R67.1
unnamed: LED42.1 (C), R68.1
unnamed: LED43.1 (C), R69.1
unnamed: LED44.1 (C), R70.1
unnamed: LED45.1 (C), R71.1
unnamed: LED46.1 (C), R72.1
unnamed: LED47.1 (C), R73.1
unnamed: LED48.1 (C), R74.1
unnamed: LED49.1 (C), R79.1
unnamed: LED50.1 (C), R80.1
unnamed: LED51.1 (C), R81.1
unnamed: LED52.1 (C), R82.1
unnamed: LED53.1 (C), R83.1
unnamed: LED54.1 (C), R84.1
unnamed: LED55.1 (C), R85.1
unnamed: LED56.1 (C), R86.1
VCC: Q1.2 (E), Q2.2 (E), Q5.2 (E), Q6.2 (E), Q9.2 (E), Q10.2 (E), Q13.2 (E); also elsewhere on the board

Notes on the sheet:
row control
column control
LED matrix

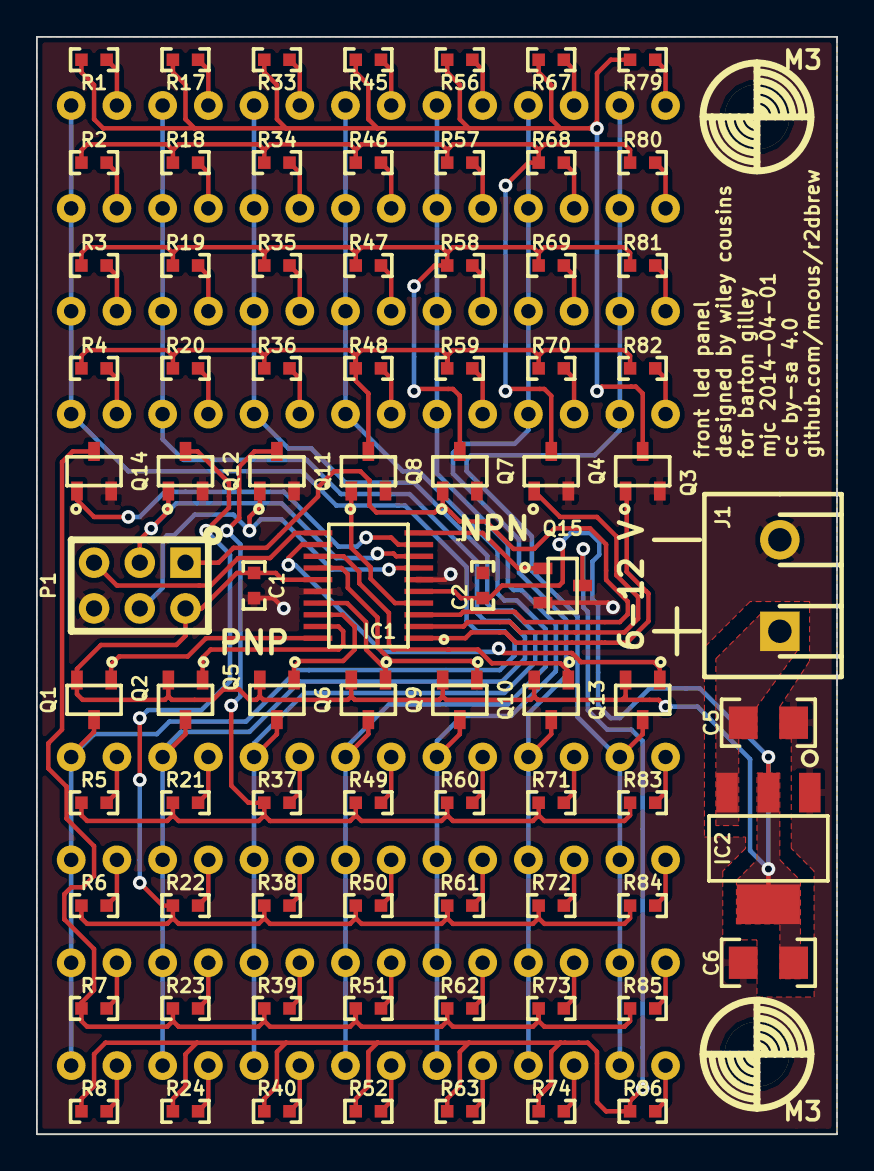
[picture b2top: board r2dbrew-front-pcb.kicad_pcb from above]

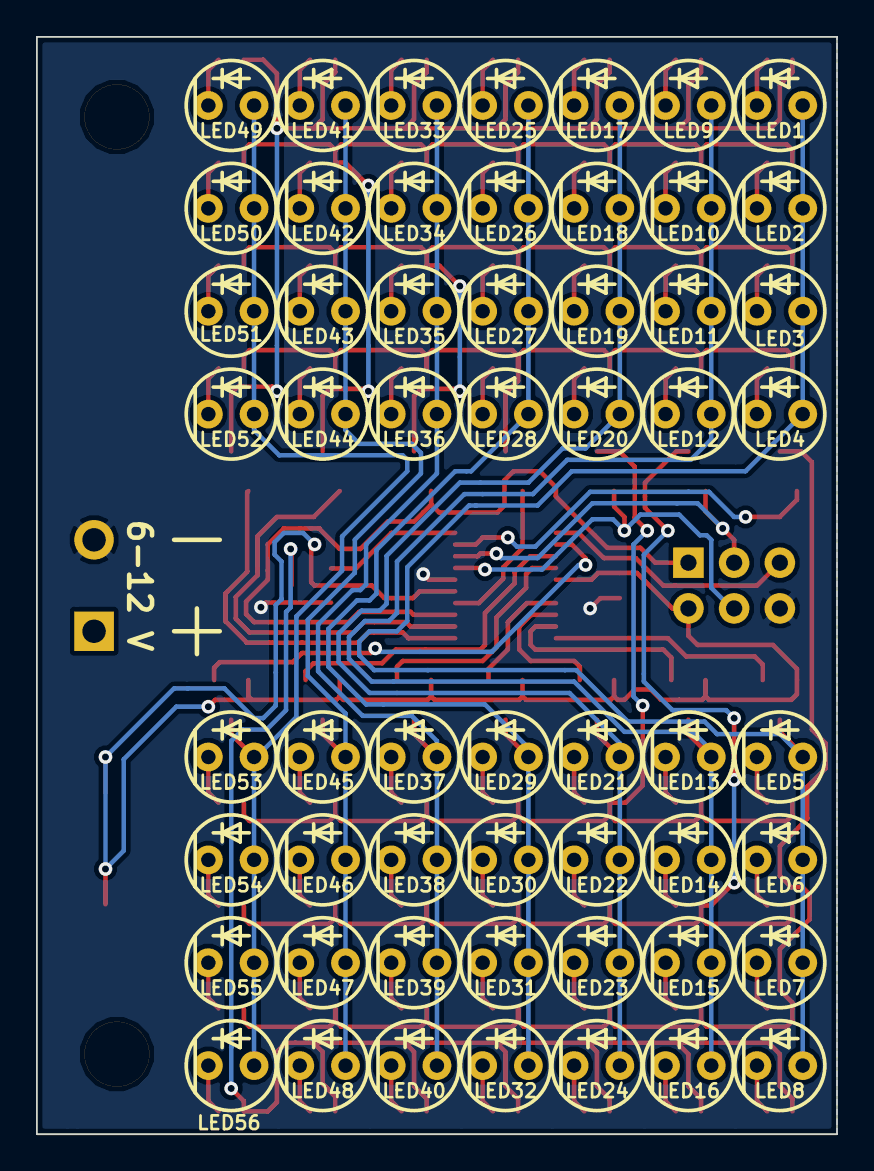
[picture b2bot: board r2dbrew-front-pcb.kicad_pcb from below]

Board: 2 copper layers, 44.5 x 61.0 mm, 137 parts (56 on the bottom side), 90 nets.

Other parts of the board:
M3, M3#2: VAL**; M3

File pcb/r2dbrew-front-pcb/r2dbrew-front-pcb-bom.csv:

"Id";"Designator";"Package";"Quantity";"Designation";"Supplier and ref";
1;"M3,M3";"M3";2;"VAL**";;;
2;"C1,C2";"passive-smd:0603(1608m)";2;"0.1uF";;;
3;"C5";"passive-smd:1206(3216m)";1;"10uF";;;
4;"C6";"passive-smd:1206(3216m)";1;"22uF";;;
5;"IC1";"sop:TSSOP20";1;"ATTINY167";;;
6;"IC2";"sot:SOT223";1;"LM1117";;;
7;"J1";"connect-thru:1x2-SCREW-TERM_P200mil";1;"6-12V";;;
8;"LED1,LED2,LED3,LED4,LED5,LED6,LED7,LED8,LED9,LED10,LED11,LED12,LED13,LED14,LED15,LED16,LED17,LED18,LED19,LED20,LED21,LED22,LED23,LED24,LED25,LED26,LED27,LED28,LED29,LED30,LED31,LED32,LED33,LED34,LED35,LED36,LED37,LED38,LED39,LED40,LED41,LED42,LED43,LED44,LED45,LED46,LED47,LED48,LED49,LED50,LED51,LED52,LED53,LED54,LED55,LED56";"led:5mm-THRU-LED";56;"LED";;;
9;"P1";"connect-thru:2x3-ARRAY_P100mil";1;"AVR_ISP";;;
10;"Q1,Q2,Q5,Q6,Q9,Q10,Q13";"sot:SOT23";7;"DDTB113ZC";;;
11;"Q3,Q4,Q7,Q8,Q11,Q12,Q14,Q15";"sot:SOT23";8;"DDTD113ZC";;;
12;"R1,R2,R3,R4,R5,R6,R7,R8,R17,R18,R19,R20,R21,R22,R23,R24,R33,R34,R35,R36,R37,R38,R39,R40,R45,R46,R47,R48,R49,R50,R51,R52,R56,R57,R58,R59,R60,R61,R62,R63,R67,R68,R69,R70,R71,R72,R73,R74,R79,R80,R81,R82,R83,R84,R85,R86";"passive-smd:0603(1608m)";56;"68Ω";;;

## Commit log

2013-11-12 getting some thoughts on "paper"
2013-11-12 ideas!
2013-11-12 initial schematic pass
2013-11-12 changing file names and directory structure around
2013-11-12 fixed up the files after rename
2013-11-13 first pass at board layout. will probably try again
2013-11-13 taking another board pass
2013-11-13 liking this placement a lot more
2014-01-22 about to redo a bunch of stuff
2014-01-22 redoing front board
2014-01-24 layout complete
2014-01-24 board layout done safety commit
2014-01-24 moving on to rear pcb
2014-01-24 back pcb schematic pass 1 done
2014-01-25 well, that wasn't so easy
2014-01-25 component selection
2014-01-28 tentative placement layout
2014-03-19 add pnale dimensions
2014-03-20 continue routing for back pcb
2014-03-20 commit for safety
2014-03-20 commit for dinner
2014-04-01 layout back board copper
2014-04-01 layout finished
2014-04-01 fix voltage regulator cap values and footprints
2014-04-01 finish back layout and rename project
2014-04-01 cleanup after project rename
2014-04-01 add read pcb schematic and gerber plots
2014-04-02 rename front board to new project name
2014-04-02 cleanup files after rename and prepare for plotting
2014-04-02 add gerber plots for front board
2014-04-02 fix rear silkscreen and mask clearance
2014-04-02 fix ic2 missing from silkscreen
2014-04-02 fix mask clearance for back board
2014-04-02 rename plots to new project name
2014-04-02 add back panel plots with correct names
2014-05-03 add back pcb bom in csv format;
2014-05-03 add front pcb bom in csv format
2014-05-03 add initial front led panel firmware
2014-05-03 switch back leds to proper orientation. fixes #1
2014-05-03 drastically improve front random display
2014-05-03 add back panel files
2014-05-03 add comments
2014-05-03 work on back panel firmware
2014-05-10 work
2014-06-14 add psi functionality

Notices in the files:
pcb/r2dbrew-back-pcb/r2dbrew-back-pcb.kicad_pcb:
shared under the terms of the Creative Commes BY-SA 4.0 License
open source hardware: cc by-sa 4.0
pcb/r2dbrew-back-pcb/r2dbrew-back-pcb.sch:
shared under the terms of the Creative Commons Attribution Share-Alike 4.0 license
pcb/r2dbrew-front-pcb/r2dbrew-front-pcb.kicad_pcb:
released under the terms of the CC BY-SA 4.0 license
cc by-sa 4.0
